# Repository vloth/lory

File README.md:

# Lory keyboard
The Lory keyboard is a low profile, ergonomic keyboard based on [Haigha 2](https://github.com/davidphilipbarr/36keys/tree/master/34Keys/Cradio-Z) from broom. 
Currently, it has no case support and it should just sit in regular bumpons.  
### [Build guide](./BUILD_GUIDE.md)  
#### [Gerbers](https://github.com/vloth/lory/releases/download/v1/gerber.zip)

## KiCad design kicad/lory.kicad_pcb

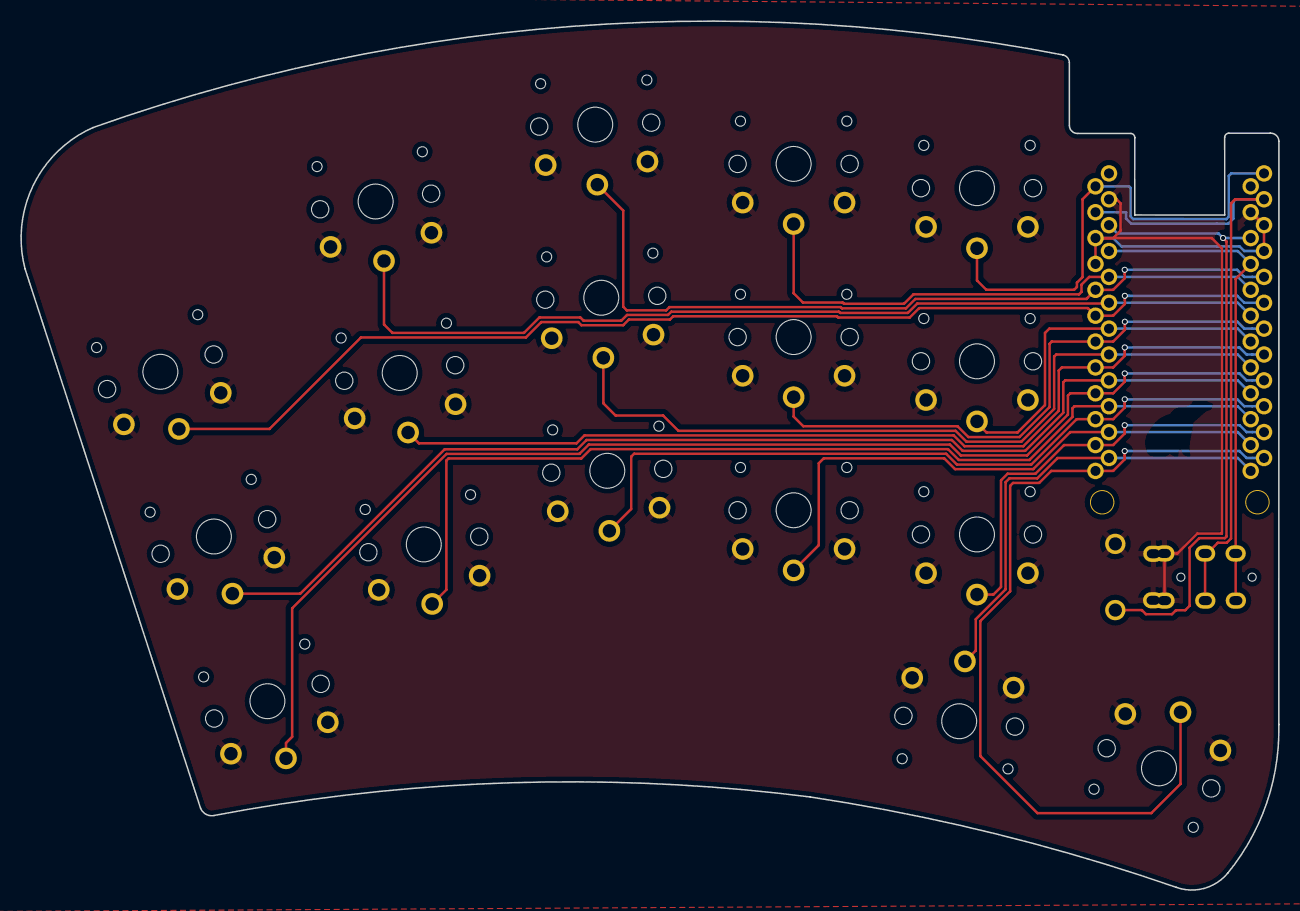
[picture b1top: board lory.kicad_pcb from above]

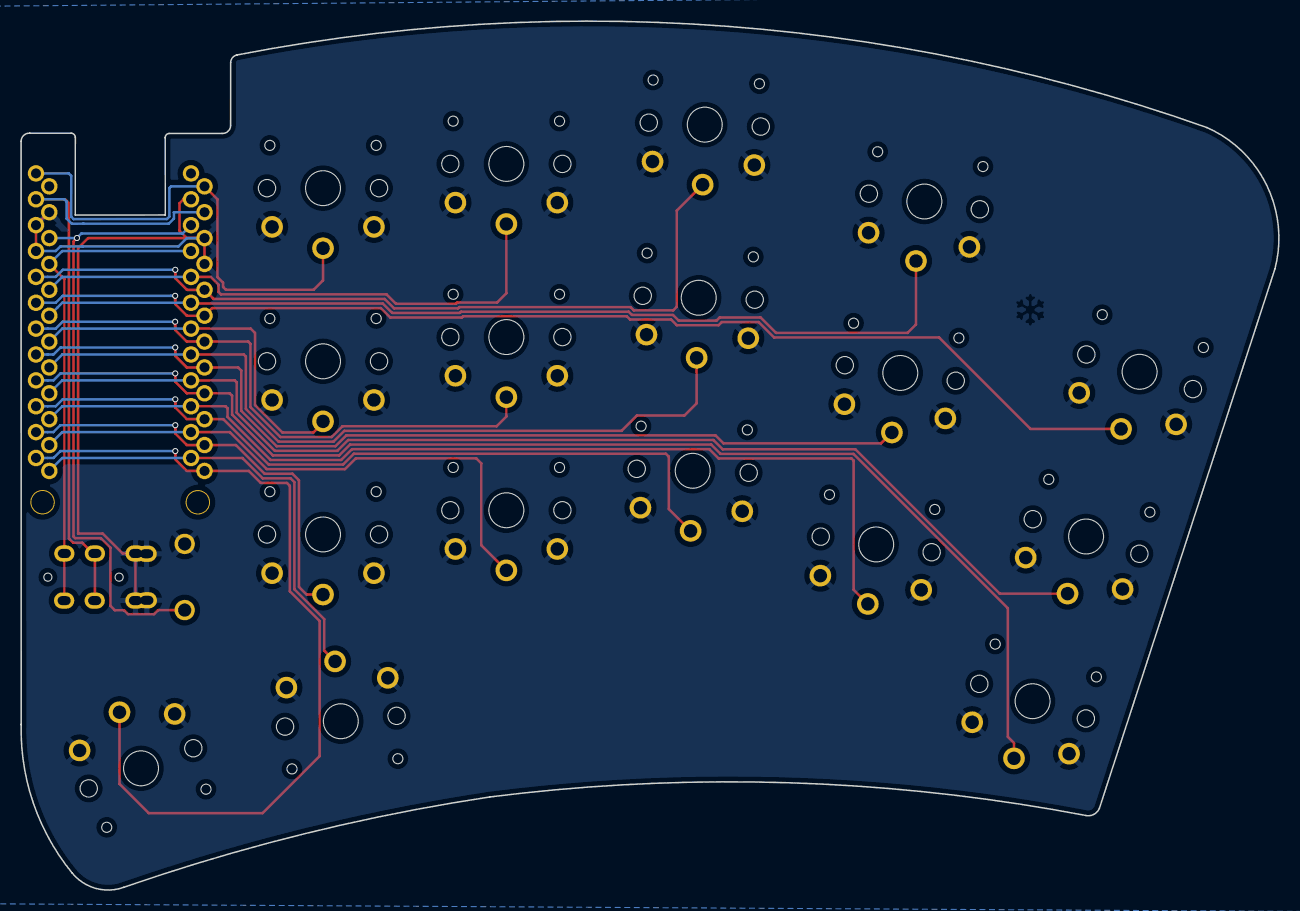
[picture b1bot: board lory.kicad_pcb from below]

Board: 2 copper layers, 123.5 x 85.3 mm, 22 parts (3 on the bottom side), 21 nets.

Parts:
J1: TRRS; TRRS-PJ-DPB2
RSW1: Val**; ResetSW
SW2, SW3, SW4, SW5, SW6, SW8, SW9, SW10, SW11, SW12, SW14, SW15, SW16, SW17, SW18, SW20, SW21: SW_PUSH; SW_PG1350_reversible_b2
U1: ProMicro; ProMicro_v2
h2, h2#2: h2; LEGO_HOLE

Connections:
GND: J1.S, J1.T, RSW1.2, SW2.2, SW3.2, SW4.2, SW5.2, SW6.2, SW8.2, SW9.2, SW10.2, SW11.2, SW12.2, SW14.2, SW15.2, SW16.2, SW17.2, SW18.2, SW20.2, SW21.2, U1.3, U1.4, U1.23
LED: SW6.1, U1.1
unnamed: SW5.1, U1.20
unnamed: SW18.1, U1.11
unnamed: SW21.1, U1.12
unnamed: SW20.1, U1.13
unnamed: SW17.1, U1.14
SCL: SW2.1, U1.6
SDA: SW4.1, U1.5
VCC: J1.R2, U1.21
col1: SW3.1, U1.19
col2: SW12.1, U1.18
col3: SW10.1, U1.17
col4: SW8.1, U1.16
col5: SW15.1, U1.15
data: J1.R1, U1.2
reset: RSW1.1, U1.22
row0: SW11.1, U1.7
row1: SW9.1, U1.8
row2: SW14.1, U1.9
row3: SW16.1, U1.10

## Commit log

2021-07-25 Add source files
2021-07-25 Add qmk firmware source code
2021-07-25 Add release link to doc
2021-07-25 Add build guide
2021-07-25 Starting V2
2021-07-26 New alpha cluster
2021-07-28 Add length info to holtie
2021-07-30 Add reset switch spec property
2021-07-30 Update footprint lib
2021-08-22 Thumbs further apart
2021-08-26 Add wiring
2021-09-10 Finish v2 start v2-oled
2021-09-10 Cleanup
2021-09-10 Added diodes
2021-09-11 Components placed
2021-10-02 temp
2021-10-06 temp opean boardline
2021-10-08 temp cluster
2021-10-08 DLC Clean
2021-10-08 Create copy pcbnew for plates
2021-10-08 Add plate cutout footprint
2021-10-08 Plate build
2021-10-08 Plate ready
2021-10-08 pm cover
2021-10-08 pm cover - mouse bites
2021-10-08 integrated mouse bite
2021-10-12 integrated mouse bite - dual bridge
2021-10-12 Add plate
